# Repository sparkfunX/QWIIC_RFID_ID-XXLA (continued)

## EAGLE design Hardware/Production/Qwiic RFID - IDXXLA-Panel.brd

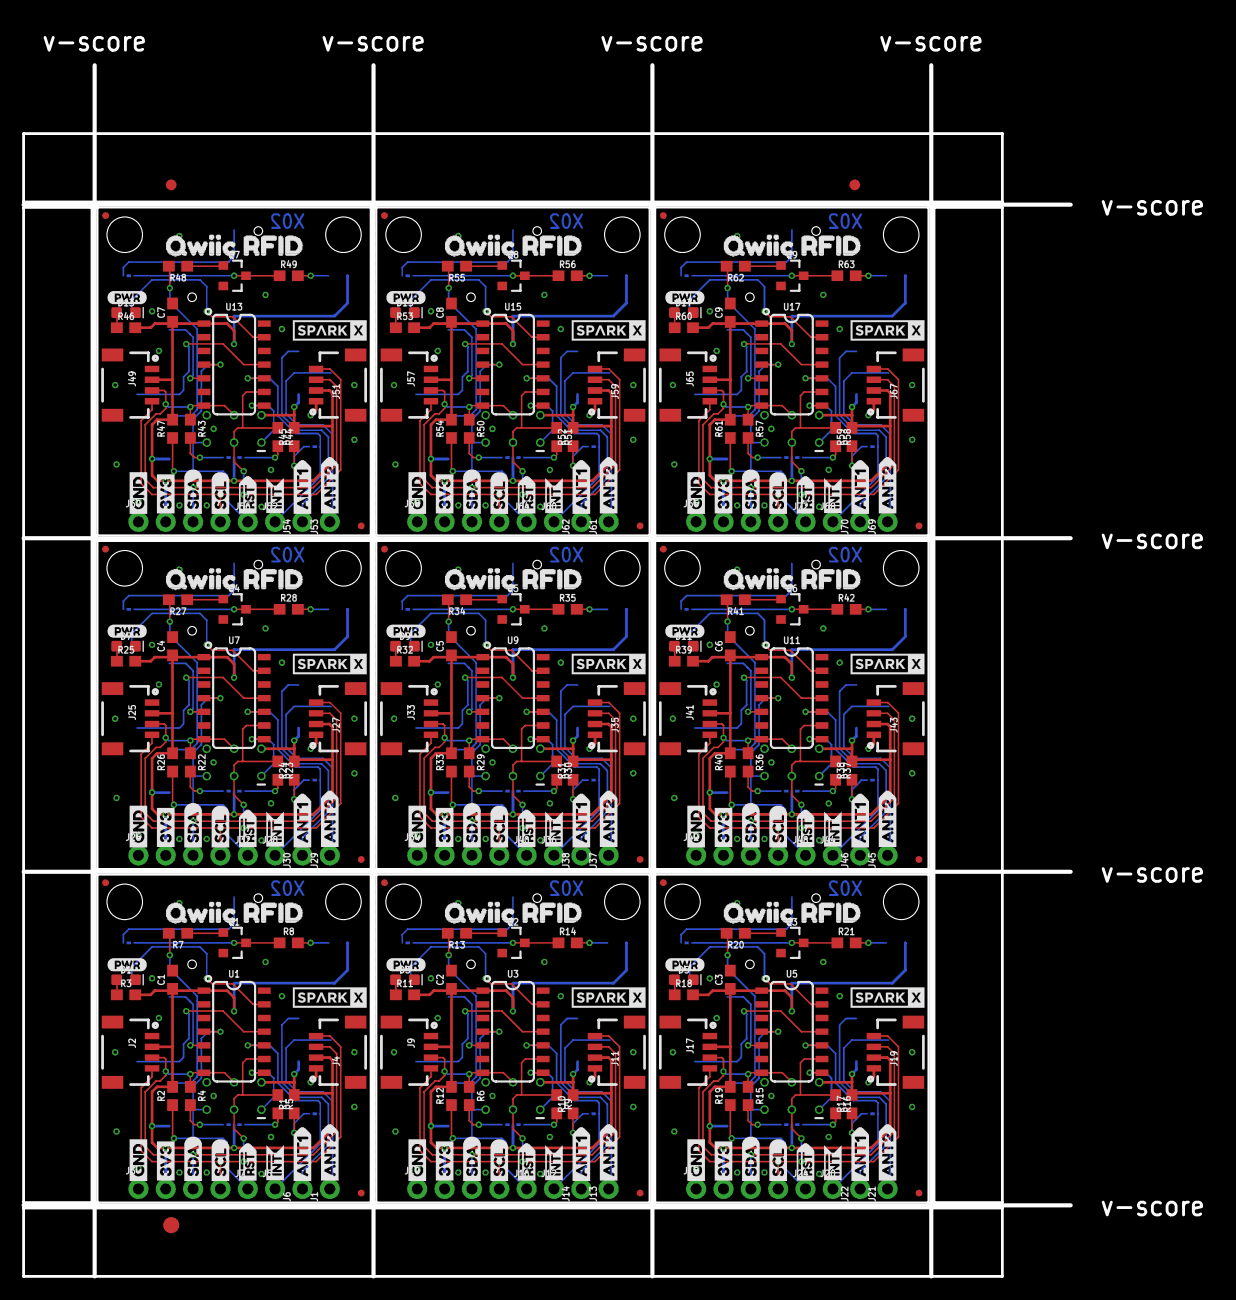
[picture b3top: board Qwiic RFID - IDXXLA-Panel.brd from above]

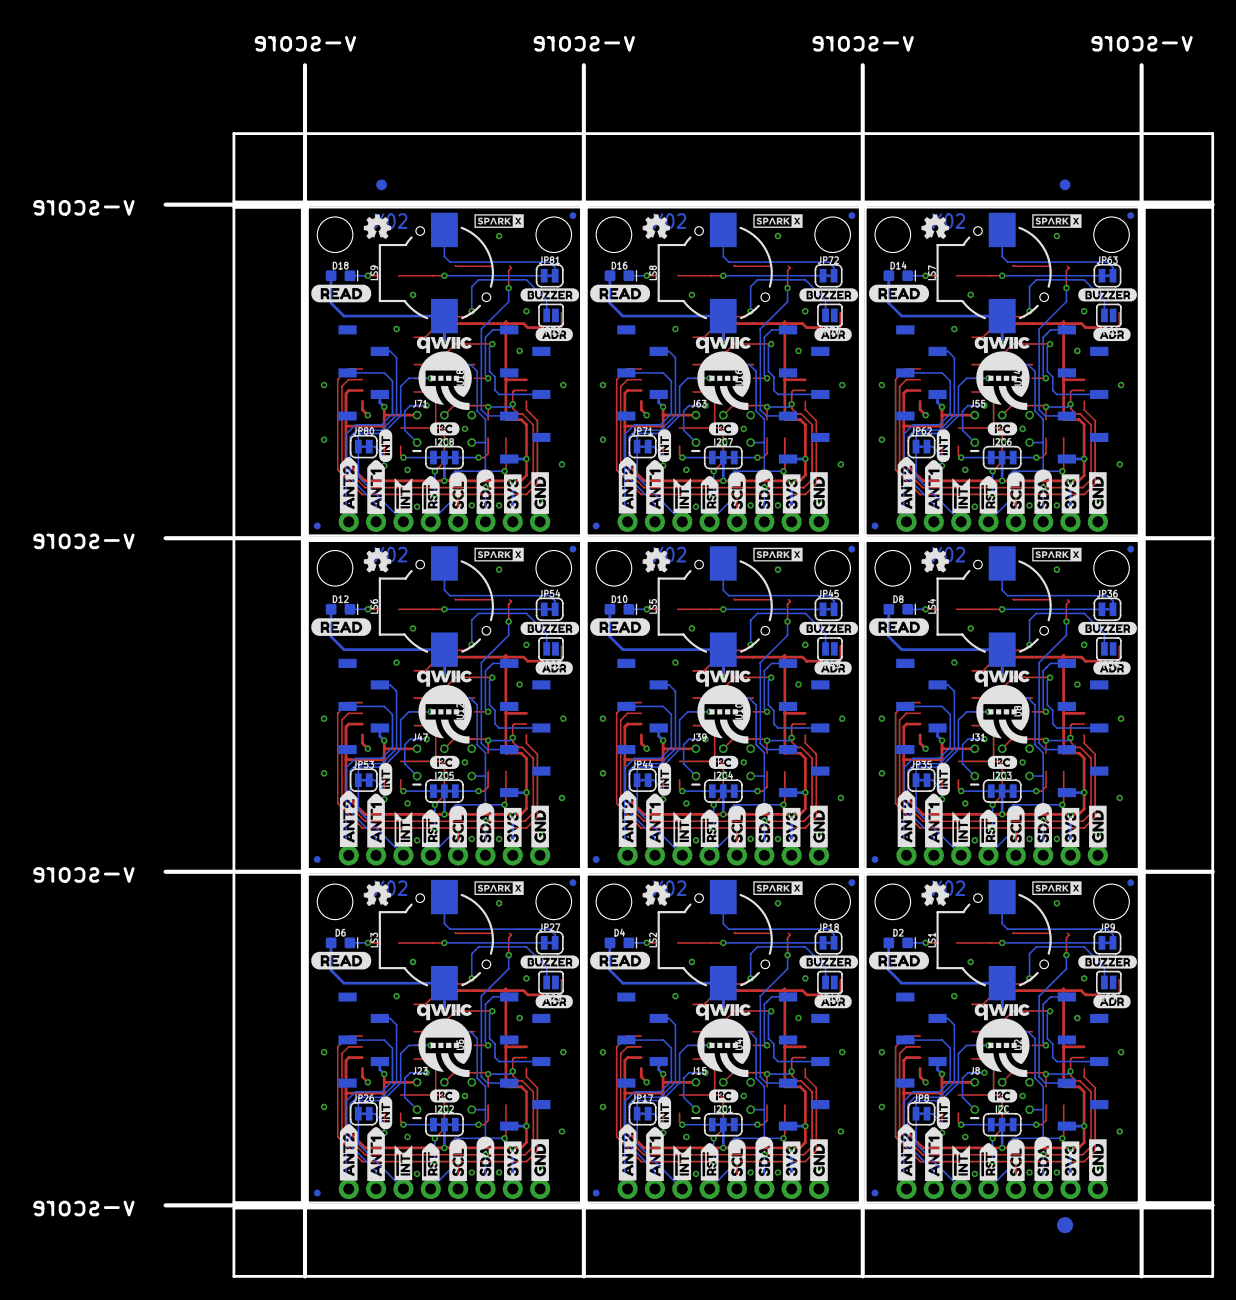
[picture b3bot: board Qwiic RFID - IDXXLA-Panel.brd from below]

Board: 2 copper layers, 110.5 x 116.4 mm, 537 parts (237 on the bottom side), 189 nets.

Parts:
C1, C2, C3, C4, C5, C6, C7, C8, C9: 0.1uF; 0603
D1, D3, D5, D7, D9, D11, D13, D15, D17: RED; LED-0603
D2, D4, D6, D8, D10, D12, D14, D16, D18: BLUE; LED-0603
E$1, E$2, E$3, E$4: FIDUCIAL-1X2
E$5, E$6: FIDUCIAL-1.5X3
I2C, I2C1, I2C2, I2C3, I2C4, I2C5, I2C6, I2C7, I2C8: SMT-JUMPER_3_2-NC_TRACE_SILK
J1, J5, J6, J7, J12, J13, J14, J16, J20, J21, J22, J24, J28, J29, J30, J32, J36, J37, J38, J40, J44, J45, J46, J48, J52, J53, J54, J56, J60, J61, J62, J64, J68, J69, J70, J72: 1X01_NO_SILK
J2, J4, J9, J11, J17, J19, J25, J27, J33, J35, J41, J43, J49, J51, J57, J59, J65, J67: SMD; 1X04_1MM_RA
J3, J10, J18, J26, J34, J42, J50, J58, J66: PTH; 1X04_NO_SILK
J8, J15, J23, J31, J39, J47, J55, J63, J71: AVR_SPI_PROG_3X2TESTPOINTS; 2X3_TEST_POINTS
JP1, JP2, JP5, JP6, JP12, JP13, JP14, JP15, JP21, JP22, JP23, JP24, JP30, JP31, JP32, JP33, JP39, JP40, JP41, JP42, JP48, JP49, JP50, JP51, JP57, JP58, JP59, JP60, JP66, JP67, JP68, JP69, JP75, JP76, JP77, JP78: FIDUCIALUFIDUCIAL; MICRO-FIDUCIAL
JP3, JP4, JP10, JP11, JP19, JP20, JP28, JP29, JP37, JP38, JP46, JP47, JP55, JP56, JP64, JP65, JP73, JP74: STAND-OFF
JP7, JP16, JP25, JP34, JP43, JP52, JP61, JP70, JP79: ADR; SMT-JUMPER_2_NO_SILK
JP8, JP17, JP26, JP35, JP44, JP53, JP62, JP71, JP80: INT; SMT-JUMPER_2_NC_TRACE_SILK
JP9, JP18, JP27, JP36, JP45, JP54, JP63, JP72, JP81: BUZZ; SMT-JUMPER_2_NC_TRACE_SILK
LOGO1, LOGO2, LOGO3, LOGO4, LOGO5, LOGO6, LOGO7, LOGO8, LOGO9: OSHW-LOGOMINI; OSHW-LOGO-MINI
LS1, LS2, LS3, LS4, LS5, LS6, LS7, LS8, LS9: BUZZER-SMD; BUZZER-CCV
Q1, Q2, Q3, Q4, Q5, Q6, Q7, Q8, Q9: 600mA/40V; SOT23-3
R1, R2, R10, R12, R17, R19, R24, R26, R31, R33, R38, R40, R45, R47, R52, R54, R59, R61: 10k; 0603
R3, R7, R8, R11, R13, R14, R18, R20, R21, R25, R27, R28, R32, R34, R35, R39, R41, R42, R46, R48, R49, R53, R55, R56, R60, R62, R63: 1k; 0603
R4, R5, R6, R9, R15, R16, R22, R23, R29, R30, R36, R37, R43, R44, R50, R51, R57, R58: 2.2k; 0603
U1, U3, U5, U7, U9, U11, U13, U15, U17: ATTINY84-ARDUINO; SO14
U2, U4, U6, U8, U10, U12, U14, U16, U18: ID-12/20SMD; ID-12_SMD
U$1, U$52, U$78, U$104, U$130, U$156, U$182, U$208, U$234: SPARKX-TINY
U$2, U$48, U$74, U$100, U$126, U$152, U$178, U$204, U$230: I_SUPER2_C-()-03
U$3, U$17, U$37, U$40, U$63, U$66, U$89, U$92, U$115, U$118, U$141, U$144, U$167, U$170, U$193, U$196, U$219, U$222: ANT20
U$4, U$28, U$54, U$80, U$106, U$132, U$158, U$184, U$210: SPARKX-LOGO3; SPARKX-SMALL
U$5, U$26, U$29, U$47, U$55, U$73, U$81, U$99, U$107, U$125, U$133, U$151, U$159, U$177, U$185, U$203, U$211, U$229: RST#-[>
U$6, U$23, U$30, U$44, U$56, U$70, U$82, U$96, U$108, U$122, U$134, U$148, U$160, U$174, U$186, U$200, U$212, U$226: SDA-[)
U$7, U$22, U$31, U$43, U$57, U$69, U$83, U$95, U$109, U$121, U$135, U$147, U$161, U$173, U$187, U$199, U$213, U$225: SCL-[)
U$8, U$27, U$53, U$79, U$105, U$131, U$157, U$183, U$209: QWIIC-LOGO-MEDIUM
U$9, U$25, U$32, U$46, U$58, U$72, U$84, U$98, U$110, U$124, U$136, U$150, U$162, U$176, U$188, U$202, U$214, U$228: GND-04
U$10, U$24, U$33, U$45, U$59, U$71, U$85, U$97, U$111, U$123, U$137, U$149, U$163, U$175, U$189, U$201, U$215, U$227: 3V3-04
U$11, U$21, U$34, U$42, U$60, U$68, U$86, U$94, U$112, U$120, U$138, U$146, U$164, U$172, U$190, U$198, U$216, U$224: INT#-[<
U$12, U$49, U$75, U$101, U$127, U$153, U$179, U$205, U$231: ADR0
U$13, U$50, U$76, U$102, U$128, U$154, U$180, U$206, U$232: INT0
U$14, U$51, U$77, U$103, U$129, U$155, U$181, U$207, U$233: PWR-()-03
U$15, U$35, U$61, U$87, U$113, U$139, U$165, U$191, U$217: BUZZER0
U$16, U$20, U$36, U$41, U$62, U$67, U$88, U$93, U$114, U$119, U$140, U$145, U$166, U$171, U$192, U$197, U$218, U$223: ANT10
U$18, U$38, U$64, U$90, U$116, U$142, U$168, U$194, U$220: READ0
U$19, U$39, U$65, U$91, U$117, U$143, U$169, U$195, U$221: QWIIC_RFID0

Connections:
3.3V: C1.1, D2.A, I2C.2, J2.2, J3.2, J4.2, J8.2, LS1.+, R1.2, R2.2, R3.2, U1.1, U2.2, U2.11
3.3V1: C2.1, D4.A, I2C1.2, J9.2, J10.2, J11.2, J15.2, LS2.+, R10.2, R11.2, R12.2, U3.1, U4.2, U4.11
3.3V2: C3.1, D6.A, I2C2.2, J17.2, J18.2, J19.2, J23.2, LS3.+, R17.2, R18.2, R19.2, U5.1, U6.2, U6.11
3.3V3: C4.1, D8.A, I2C3.2, J25.2, J26.2, J27.2, J31.2, LS4.+, R24.2, R25.2, R26.2, U7.1, U8.2, U8.11
3.3V4: C5.1, D10.A, I2C4.2, J33.2, J34.2, J35.2, J39.2, LS5.+, R31.2, R32.2, R33.2, U9.1, U10.2, U10.11
3.3V5: C6.1, D12.A, I2C5.2, J41.2, J42.2, J43.2, J47.2, LS6.+, R38.2, R39.2, R40.2, U11.1, U12.2, U12.11
3.3V6: C7.1, D14.A, I2C6.2, J49.2, J50.2, J51.2, J55.2, LS7.+, R45.2, R46.2, R47.2, U13.1, U14.2, U14.11
3.3V7: C8.1, D16.A, I2C7.2, J57.2, J58.2, J59.2, J63.2, LS8.+, R52.2, R53.2, R54.2, U15.1, U16.2, U16.11
3.3V8: C9.1, D18.A, I2C8.2, J65.2, J66.2, J67.2, J71.2, LS9.+, R59.2, R60.2, R61.2, U17.1, U18.2, U18.11
!INT: J5.1, JP8.1, U1.10
!INT1: J12.1, JP17.1, U3.10
!INT2: J20.1, JP26.1, U5.10
!INT3: J28.1, JP35.1, U7.10
!INT4: J36.1, JP44.1, U9.10
!INT5: J44.1, JP53.1, U11.10
!INT6: J52.1, JP62.1, U13.10
!INT7: J60.1, JP71.1, U15.10
!INT8: J68.1, JP80.1, U17.10
!RST: J7.1, J8.5, R2.1, U1.4
!RST1: J15.5, J16.1, R12.1, U3.4
!RST2: J23.5, J24.1, R19.1, U5.4
!RST3: J31.5, J32.1, R26.1, U7.4
!RST4: J39.5, J40.1, R33.1, U9.4
!RST5: J47.5, J48.1, R40.1, U11.4
!RST6: J55.5, J56.1, R47.1, U13.4
!RST7: J63.5, J64.1, R54.1, U15.4
!RST8: J71.5, J72.1, R61.1, U17.4
ANT1: J1.1, U2.3
ANT2: J6.1, U2.4
ANT3: J13.1, U4.3
ANT4: J14.1, U4.4
ANT5: J21.1, U6.3
ANT6: J22.1, U6.4
ANT7: J29.1, U8.3
ANT8: J30.1, U8.4
ANT9: J37.1, U10.3
ANT10: J38.1, U10.4
ANT11: J45.1, U12.3
ANT12: J46.1, U12.4
ANT13: J53.1, U14.3
ANT14: J54.1, U14.4
ANT15: J61.1, U16.3
ANT16: J62.1, U16.4
ANT17: J69.1, U18.3
ANT18: J70.1, U18.4
DATA_UART: U1.11, U2.9
DATA_UART1: U3.11, U4.9
DATA_UART2: U5.11, U6.9
DATA_UART3: U7.11, U8.9
DATA_UART4: U9.11, U10.9
DATA_UART5: U11.11, U12.9
DATA_UART6: U13.11, U14.9
DATA_UART7: U15.11, U16.9
DATA_UART8: U17.11, U18.9
GND: C1.2, D1.C, J2.1, J3.1, J4.1, J8.6, JP7.1, Q1.2, U1.14, U2.1, U2.7
GND1: C2.2, D3.C, J9.1, J10.1, J11.1, J15.6, JP16.1, Q2.2, U3.14, U4.1, U4.7
GND2: C3.2, D5.C, J17.1, J18.1, J19.1, J23.6, JP25.1, Q3.2, U5.14, U6.1, U6.7
GND3: C4.2, D7.C, J25.1, J26.1, J27.1, J31.6, JP34.1, Q4.2, U7.14, U8.1, U8.7
GND4: C5.2, D9.C, J33.1, J34.1, J35.1, J39.6, JP43.1, Q5.2, U9.14, U10.1, U10.7
GND5: C6.2, D11.C, J41.1, J42.1, J43.1, J47.6, JP52.1, Q6.2, U11.14, U12.1, U12.7
GND6: C7.2, D13.C, J49.1, J50.1, J51.1, J55.6, JP61.1, Q7.2, U13.14, U14.1, U14.7
GND7: C8.2, D15.C, J57.1, J58.1, J59.1, J63.6, JP70.1, Q8.2, U15.14, U16.1, U16.7
GND8: C9.2, D17.C, J65.1, J66.1, J67.1, J71.6, JP79.1, Q9.2, U17.14, U18.1, U18.7
LED_BUZZ: R7.2, U2.10
LED_BUZZ1: R13.2, U4.10
LED_BUZZ2: R20.2, U6.10
LED_BUZZ3: R27.2, U8.10
LED_BUZZ4: R34.2, U10.10
LED_BUZZ5: R41.2, U12.10
LED_BUZZ6: R48.2, U14.10
LED_BUZZ7: R55.2, U16.10
LED_BUZZ8: R62.2, U18.10
MISO: J8.1, U1.8
MISO1: J15.1, U3.8
MISO2: J23.1, U5.8
MISO3: J31.1, U7.8
MISO4: J39.1, U9.8
MISO5: J47.1, U11.8
MISO6: J55.1, U13.8
MISO7: J63.1, U15.8
MISO8: J71.1, U17.8
unnamed: I2C.1, R5.2
unnamed: I2C.3, R4.2
unnamed: D1.A, R3.1
unnamed: JP8.2, R1.1
unnamed: D2.C, R8.2
unnamed: JP7.2, U1.13
unnamed: Q1.1, R7.1
unnamed: JP9.1, Q1.3, R8.1
unnamed: JP9.2, LS1.-
unnamed: I2C1.1, R9.2
unnamed: D3.A, R11.1
unnamed: JP16.2, U3.13
unnamed: I2C1.3, R6.2
unnamed: JP17.2, R10.1
unnamed: Q2.1, R13.1
unnamed: JP18.1, Q2.3, R14.1
unnamed: D4.C, R14.2
unnamed: JP18.2, LS2.-
unnamed: I2C2.1, R16.2
unnamed: D5.A, R18.1
unnamed: JP25.2, U5.13
unnamed: I2C2.3, R15.2
unnamed: JP26.2, R17.1
unnamed: Q3.1, R20.1
unnamed: JP27.1, Q3.3, R21.1
unnamed: D6.C, R21.2
unnamed: JP27.2, LS3.-
unnamed: I2C3.1, R23.2
unnamed: D7.A, R25.1
unnamed: JP34.2, U7.13
unnamed: I2C3.3, R22.2
unnamed: JP35.2, R24.1
unnamed: Q4.1, R27.1
unnamed: JP36.1, Q4.3, R28.1
unnamed: D8.C, R28.2
unnamed: JP36.2, LS4.-
unnamed: I2C4.1, R30.2
unnamed: D9.A, R32.1
unnamed: JP43.2, U9.13
unnamed: I2C4.3, R29.2
unnamed: JP44.2, R31.1
unnamed: Q5.1, R34.1
unnamed: JP45.1, Q5.3, R35.1
unnamed: D10.C, R35.2
unnamed: JP45.2, LS5.-
unnamed: I2C5.1, R37.2
unnamed: D11.A, R39.1
unnamed: JP52.2, U11.13
unnamed: I2C5.3, R36.2
unnamed: JP53.2, R38.1
unnamed: Q6.1, R41.1
unnamed: JP54.1, Q6.3, R42.1
unnamed: D12.C, R42.2
unnamed: JP54.2, LS6.-
unnamed: I2C6.1, R44.2
unnamed: D13.A, R46.1
unnamed: JP61.2, U13.13
unnamed: I2C6.3, R43.2
unnamed: JP62.2, R45.1
unnamed: Q7.1, R48.1
unnamed: JP63.1, Q7.3, R49.1
unnamed: D14.C, R49.2
unnamed: JP63.2, LS7.-
unnamed: I2C7.1, R51.2
unnamed: D15.A, R53.1
unnamed: JP70.2, U15.13
unnamed: I2C7.3, R50.2
unnamed: JP71.2, R52.1
unnamed: Q8.1, R55.1
unnamed: JP72.1, Q8.3, R56.1
unnamed: D16.C, R56.2
unnamed: JP72.2, LS8.-
unnamed: I2C8.1, R58.2
unnamed: D17.A, R60.1
unnamed: JP79.2, U17.13
unnamed: I2C8.3, R57.2
unnamed: JP80.2, R59.1
unnamed: Q9.1, R62.1
unnamed: JP81.1, Q9.3, R63.1
unnamed: D18.C, R63.2
unnamed: JP81.2, LS9.-
SCL/SCK: J2.4, J3.4, J4.4, J8.3, R5.1, U1.9
SCL/SCK1: J9.4, J10.4, J11.4, J15.3, R9.1, U3.9
SCL/SCK2: J17.4, J18.4, J19.4, J23.3, R16.1, U5.9
SCL/SCK3: J25.4, J26.4, J27.4, J31.3, R23.1, U7.9
SCL/SCK4: J33.4, J34.4, J35.4, J39.3, R30.1, U9.9
SCL/SCK5: J41.4, J42.4, J43.4, J47.3, R37.1, U11.9
SCL/SCK6: J49.4, J50.4, J51.4, J55.3, R44.1, U13.9
SCL/SCK7: J57.4, J58.4, J59.4, J63.3, R51.1, U15.9
SCL/SCK8: J65.4, J66.4, J67.4, J71.3, R58.1, U17.9
SDA/MOSI: J2.3, J3.3, J4.3, J8.4, R4.1, U1.7
SDA/MOSI1: J9.3, J10.3, J11.3, J15.4, R6.1, U3.7
SDA/MOSI2: J17.3, J18.3, J19.3, J23.4, R15.1, U5.7
SDA/MOSI3: J25.3, J26.3, J27.3, J31.4, R22.1, U7.7
SDA/MOSI4: J33.3, J34.3, J35.3, J39.4, R29.1, U9.7
SDA/MOSI5: J41.3, J42.3, J43.3, J47.4, R36.1, U11.7
SDA/MOSI6: J49.3, J50.3, J51.3, J55.4, R43.1, U13.7
SDA/MOSI7: J57.3, J58.3, J59.3, J63.4, R50.1, U15.7
SDA/MOSI8: J65.3, J66.3, J67.3, J71.4, R57.1, U17.7
TAG_IN_RANGE: U1.5, U2.6
TAG_IN_RANGE1: U3.5, U4.6
TAG_IN_RANGE2: U5.5, U6.6
TAG_IN_RANGE3: U7.5, U8.6
TAG_IN_RANGE4: U9.5, U10.6
TAG_IN_RANGE5: U11.5, U12.6
TAG_IN_RANGE6: U13.5, U14.6
TAG_IN_RANGE7: U15.5, U16.6
TAG_IN_RANGE8: U17.5, U18.6

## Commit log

2018-06-26 Schematic organization
2018-06-26 Moved to double sided to decrease size of product
    Buzzer, LED, and RFID connector live on top.
2018-06-26 Renamed to incorporate all possible RFID modules
2018-06-26 More compact
    Shrunk 10 mil, beefed up 3.3V lines to 10 mil
2018-06-27 5 mil smaller
    Moved power LED around, squished the PCB a little more.
2018-06-27 Moved RST clost to INT PTH, better routing
2018-06-27 Production Panel 3x3
2018-06-29 Initial Code Commit
2018-07-05 Code almost done (comments need to be fleshed out)
2018-07-12 Firmware almost finalized, I2C data lines and UART lines fixed on board
2018-07-13 Minor changes to traces
2018-07-13 Panel for x02
2018-07-16 Fixed DRC erros added latest panel for x02
2018-07-16 Example sketches for the user
2018-07-18 Some comment adjustments to all example/firmware code
2018-07-27 Some array size erros, added datasheet
2018-08-02 Cleanup and ReadMe
2018-08-02 woops
2018-10-19 Fixes to README
2018-11-09 Jig for testing/programming
